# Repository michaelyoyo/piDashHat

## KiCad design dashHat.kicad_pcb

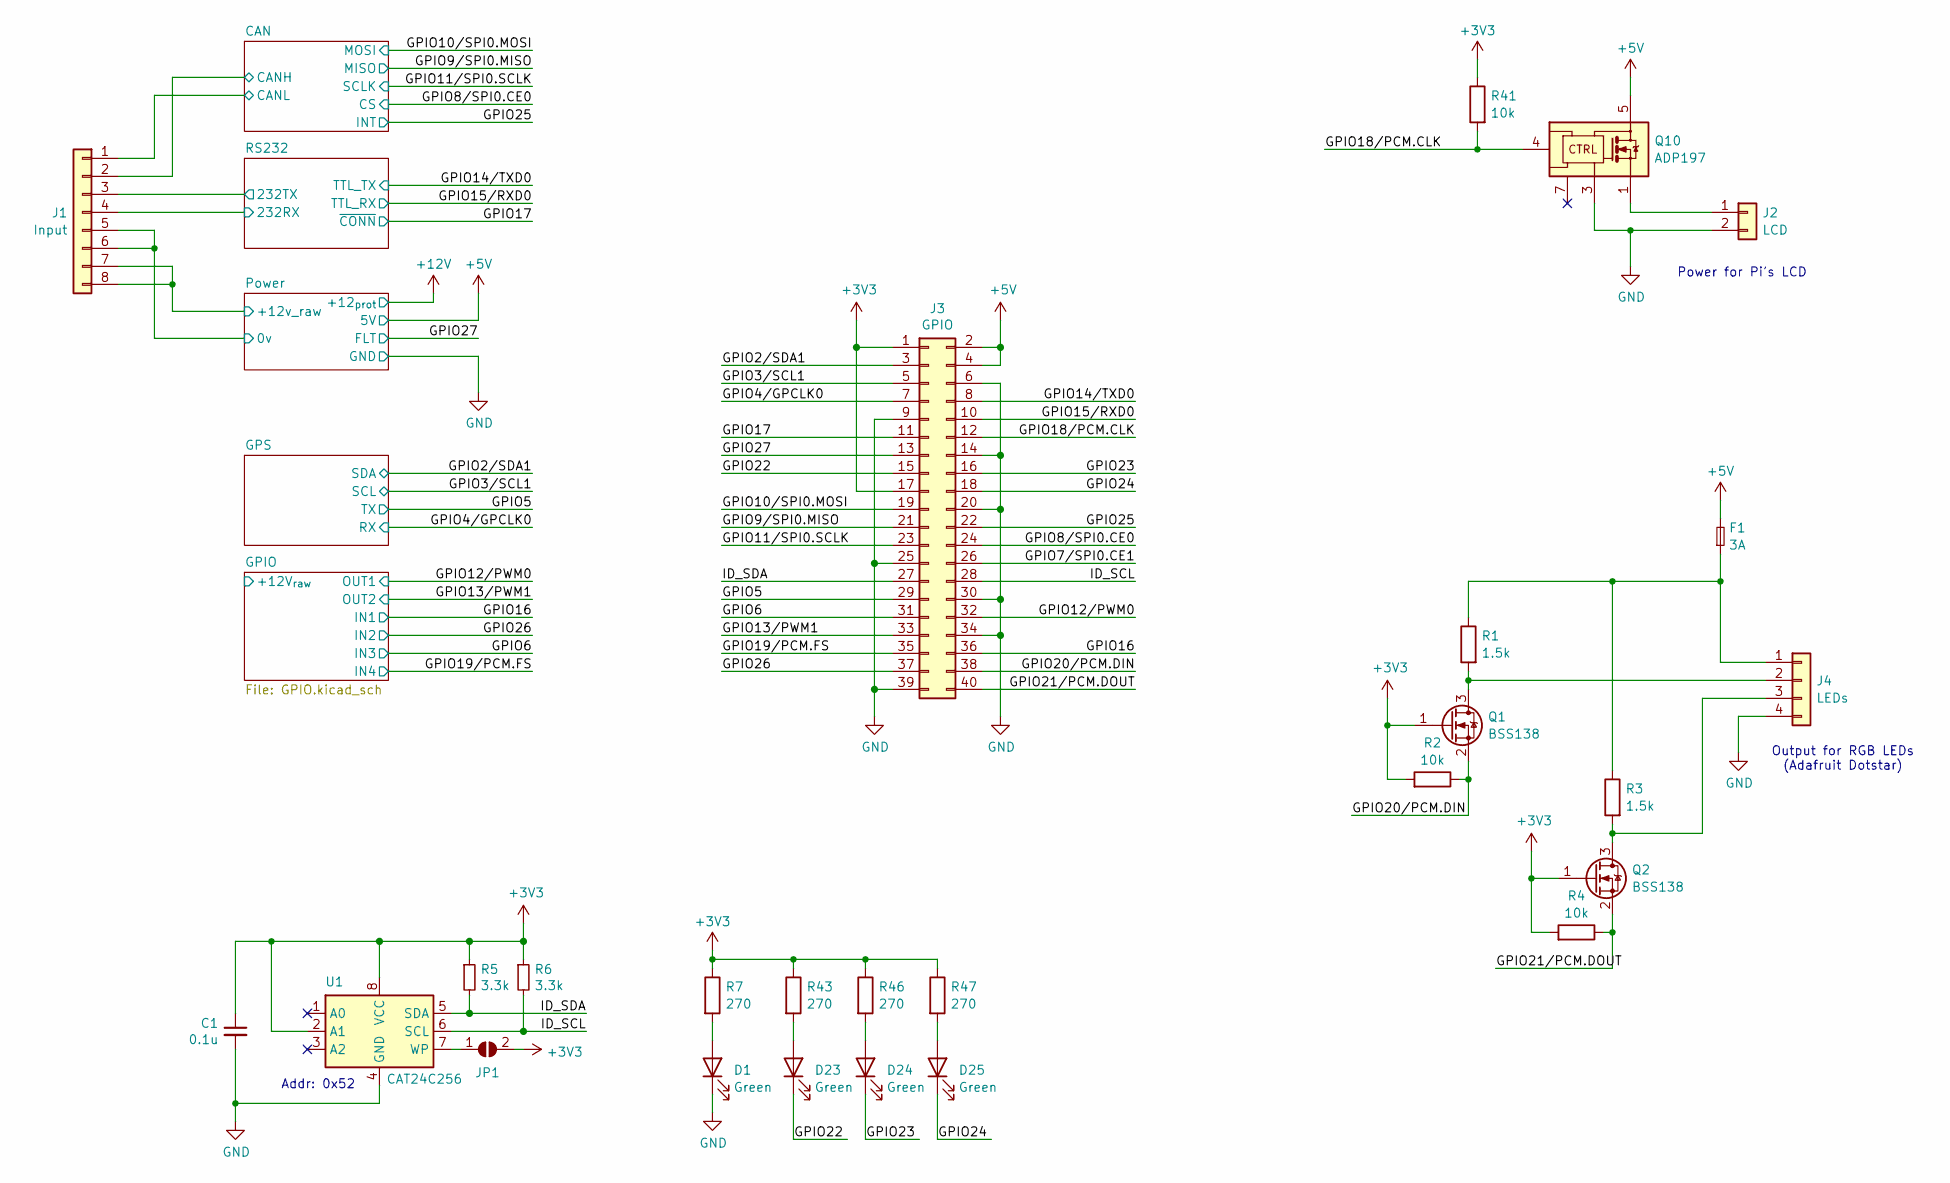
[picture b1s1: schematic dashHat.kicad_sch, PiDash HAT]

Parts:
C1: 0.1u; C_0603_1608Metric; Mfg Part Number CGA3E2X8R1E104K080AA
D1, D23, D24, D25: Green; LED_0603_1608Metric; Mfg Part Number HSMG-C190
F1: 3A; Fuse_1812_4532Metric; Mfg Part Number 0ZCG0260BF2B
J1: Input; Molex_Nano-Fit_105310-xx08_2x04_P2.50mm_Vertical; Mfg Part Number 105310-1108
J2: LCD; JST_XH_B2B-XH-A_1x02_P2.50mm_Vertical; Mfg Part Number --
J3: GPIO; PinSocket_2x20_P2.54mm_Vertical; Mfg Part Number SSQ-120-01-F-D
J4: LEDs; Molex_Nano-Fit_105310-xx04_2x02_P2.50mm_Vertical; Mfg Part Number 105310-1104
JP1: ID_WP; SolderJumper-2_P1.3mm_Open_RoundedPad1.0x1.5mm; Mfg Part Number --
Q1, Q2: BSS138; SOT-23; Mfg Part Number BSS138
Q10: ADP197; DFN-6-1EP_2x2mm_P0.65mm_EP1x1.6mm; Mfg Part Number ADP197ACPZN-01-R7
R1, R3: 1.5k; R_0603_1608Metric
R2, R4, R41: 10k; R_0603_1608Metric
R5, R6: 3.3k; R_0603_1608Metric
R7, R43, R46, R47: 270; R_0603_1608Metric
U1: CAT24C256; DFN-8-1EP_3x2mm_P0.5mm_EP1.36x1.46mm; Mfg Part Number CAT24C256HU4IGT3

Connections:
+3V3: C1.1, J3.1, J3.17, JP1.2 (B), Q1.1 (G), Q2.1 (G), R2.2, R4.2, R5.1, R6.1, R7.1, R41.1, R43.1, R46.1, R47.1, U1.2 (A1), U1.8 (VCC); also elsewhere on the board
+5V: F1.2, J3.2, J3.4, Q10.5 (VCC), Q10.6 (VCC); also elsewhere on the board
/CAN/CANH: J1.2; also elsewhere on the board
/CAN/CANL: J1.1; also elsewhere on the board
/GPIO2/SDA1: J3.3; also elsewhere on the board
/GPIO3/SCL1: J3.5; also elsewhere on the board
/GPIO4/GPCLK0: J3.7; also elsewhere on the board
/GPIO5: J3.29; also elsewhere on the board
/GPIO6: J3.31; also elsewhere on the board
/GPIO7/SPI0.CE1: J3.26
/GPIO8/SPI0.CE0: J3.24; also elsewhere on the board
/GPIO9/SPI0.MISO: J3.21; also elsewhere on the board
/GPIO10/SPI0.MOSI: J3.19; also elsewhere on the board
/GPIO11/SPI0.SCLK: J3.23; also elsewhere on the board
/GPIO12/PWM0: J3.32; also elsewhere on the board
/GPIO13/PWM1: J3.33; also elsewhere on the board
/GPIO14/TXD0: J3.8; also elsewhere on the board
/GPIO15/RXD0: J3.10; also elsewhere on the board
/GPIO16: J3.36; also elsewhere on the board
/GPIO17: J3.11; also elsewhere on the board
/GPIO18/PCM.CLK: J3.12, Q10.4 (EN), R41.2
/GPIO19/PCM.FS: J3.35; also elsewhere on the board
/GPIO20/PCM.DIN: J3.38, Q1.2 (S), R2.1
/GPIO21/PCM.DOUT: J3.40, Q2.2 (S), R4.1
/GPIO22: D23.1 (K), J3.15
/GPIO23: D24.1 (K), J3.16
/GPIO24: D25.1 (K), J3.18
/GPIO25: J3.22; also elsewhere on the board
/GPIO26: J3.37; also elsewhere on the board
/GPIO27: J3.13; also elsewhere on the board
/ID_SCL: J3.28, R6.2, U1.6 (SCL)
/ID_SDA: J3.27, R5.2, U1.5 (SDA)
/Power/+12v_raw: J1.7, J1.8; also elsewhere on the board
/RS232/232RX: J1.4; also elsewhere on the board
/RS232/232TX: J1.3; also elsewhere on the board
GND: C1.2, D1.1 (K), J1.5, J1.6, J2.2, J3.6, J3.9, J3.14, J3.20, J3.25, J3.30, J3.34, J3.39, J4.4, Q10.3 (GND), U1.4 (GND); also elsewhere on the board
unnamed: D1.2 (A), R7.2
unnamed: D23.2 (A), R43.2
unnamed: D24.2 (A), R46.2
unnamed: D25.2 (A), R47.2
unnamed: J2.1, Q10.1 (OUT), Q10.2 (OUT)
unnamed: F1.1, J4.1, R1.1, R3.1
unnamed: J4.2, Q1.3 (D), R1.2
unnamed: J4.3, Q2.3 (D), R3.2
unnamed: JP1.1 (A), U1.7 (WP)

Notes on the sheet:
Output for RGB LEDs (Adafruit Dotstar)
Addr: 0x52
Power for Pi's LCD

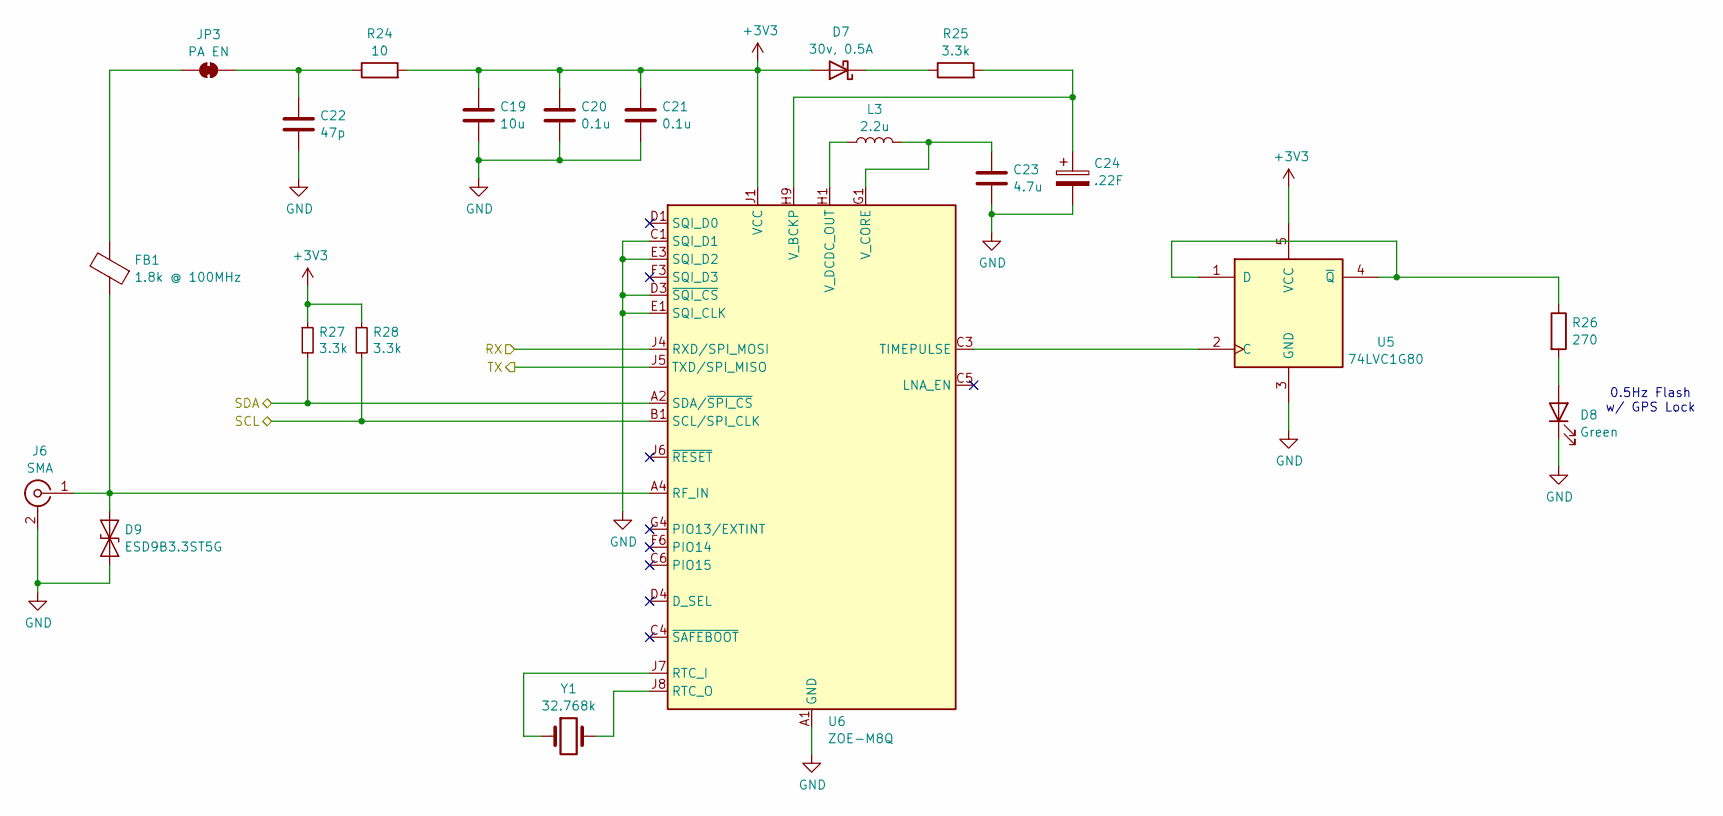
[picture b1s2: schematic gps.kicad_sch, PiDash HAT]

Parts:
C19: 10u; C_1206_3216Metric; Mfg Part Number CGA5L1X7R1C106K160AC
C20, C21: 0.1u; C_0603_1608Metric; Mfg Part Number CGA3E2X8R1E104K080AA
C22: 47p; C_0603_1608Metric; Mfg Part Number C0603C470K5RACAUTO
C23: 4.7u; C_0603_1608Metric; Mfg Part Number GCJ188C70J475KE02D
C24: .22F; DX_5R5HxxxxU_D11.5mm_P10.00mm; Mfg Part Number EDS224Z3R6H
D7: 30v, 0.5A; D_SOD-323HE; Mfg Part Number RSX051VYM30FHTR
D8: Green; LED_0603_1608Metric; Mfg Part Number HSMG-C190
D9: ESD9B3.3ST5G; D_SOD-923; Mfg Part Number ESD9R3.3ST5G
FB1: 1.8k @ 100MHz; L_0402_1005Metric; Mfg Part Number BLM15HD182SN1D
J6: SMA; SMA_Amphenol_132289_EdgeMount; Mfg Part Number 132289
JP3: PA EN; SolderJumper-2_P1.3mm_Open_RoundedPad1.0x1.5mm; Mfg Part Number --
L3: 2.2u; L_0806_2016Metric; Mfg Part Number LQM2MPN2R2NG0L
R24: 10; R_0603_1608Metric
R25, R27, R28: 3.3k; R_0603_1608Metric
R26: 270; R_0603_1608Metric
U5: 74LVC1G80; SOT-353_SC-70-5; Mfg Part Number 74LVC1G80GW,125
U6: ZOE-M8Q; ublox_ZOE_M8; Mfg Part Number ZOE-M8Q-0
Y1: 32.768k; Crystal_SMD_2012-2Pin_2.0x1.2mm; Mfg Part Number CM8V-T1A-32.768kHz-12.5pF-20PPM-TA-QC

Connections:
+3V3: C19.1, C20.1, C21.1, D7.2 (A), R24.2, R27.1, R28.1, U5.5 (VCC), U6.J1 (VCC), U6.J2 (VCC); also elsewhere on the board
/GPIO2/SDA1: R27.2, U6.A2 (SDA/~SPI_CS); also elsewhere on the board
/GPIO3/SCL1: R28.2, U6.B1 (SCL/SPI_CLK); also elsewhere on the board
/GPIO4/GPCLK0: U6.J4 (RXD/SPI_MOSI); also elsewhere on the board
/GPIO5: U6.J5 (TXD/SPI_MISO); also elsewhere on the board
GND: C19.2, C20.2, C21.2, C22.2, C23.2, C24.2, D8.1 (K), D9.1 (A1), J6.2 (Ext), U5.3 (GND), U6.A1 (GND), U6.A3 (GND), U6.A5 (GND), U6.A7 (GND), U6.A8 (GND), U6.A9 (GND), U6.B9 (GND), U6.C1 (SQI_D1), U6.C7 (GND), U6.C9 (GND), U6.D3 (~SQI_CS), U6.D6 (GND), U6.D9 (GND), U6.E1 (SQI_CLK), U6.E3 (SQI_D2), U6.E7 (GND), U6.F7 (GND), U6.G3 (GND), U6.G6 (GND), U6.G7 (GND), U6.J3 (GND), U6.J9 (GND); also elsewhere on the board
unnamed: D7.1 (K), R25.1
unnamed: D8.2 (A), R26.2
unnamed: D9.2 (A2), FB1.1, J6.1 (In), U6.A4 (RF_IN)
unnamed: C22.1, JP3.1 (A), R24.1
unnamed: FB1.2, JP3.2 (B)
unnamed: U5.2 (C), U6.C3 (TIMEPULSE)
unnamed: R26.1, U5.1 (D), U5.4 (~Q)
unnamed: U6.J7 (RTC_I), Y1.1
unnamed: U6.J8 (RTC_O), Y1.2
unnamed: C24.1, R25.2, U6.H9 (V_BCKP)
unnamed: C23.1, L3.2, U6.G1 (V_CORE)
unnamed: L3.1, U6.H1 (V_DCDC_OUT)

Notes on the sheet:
0.5Hz Flash w/ GPS Lock

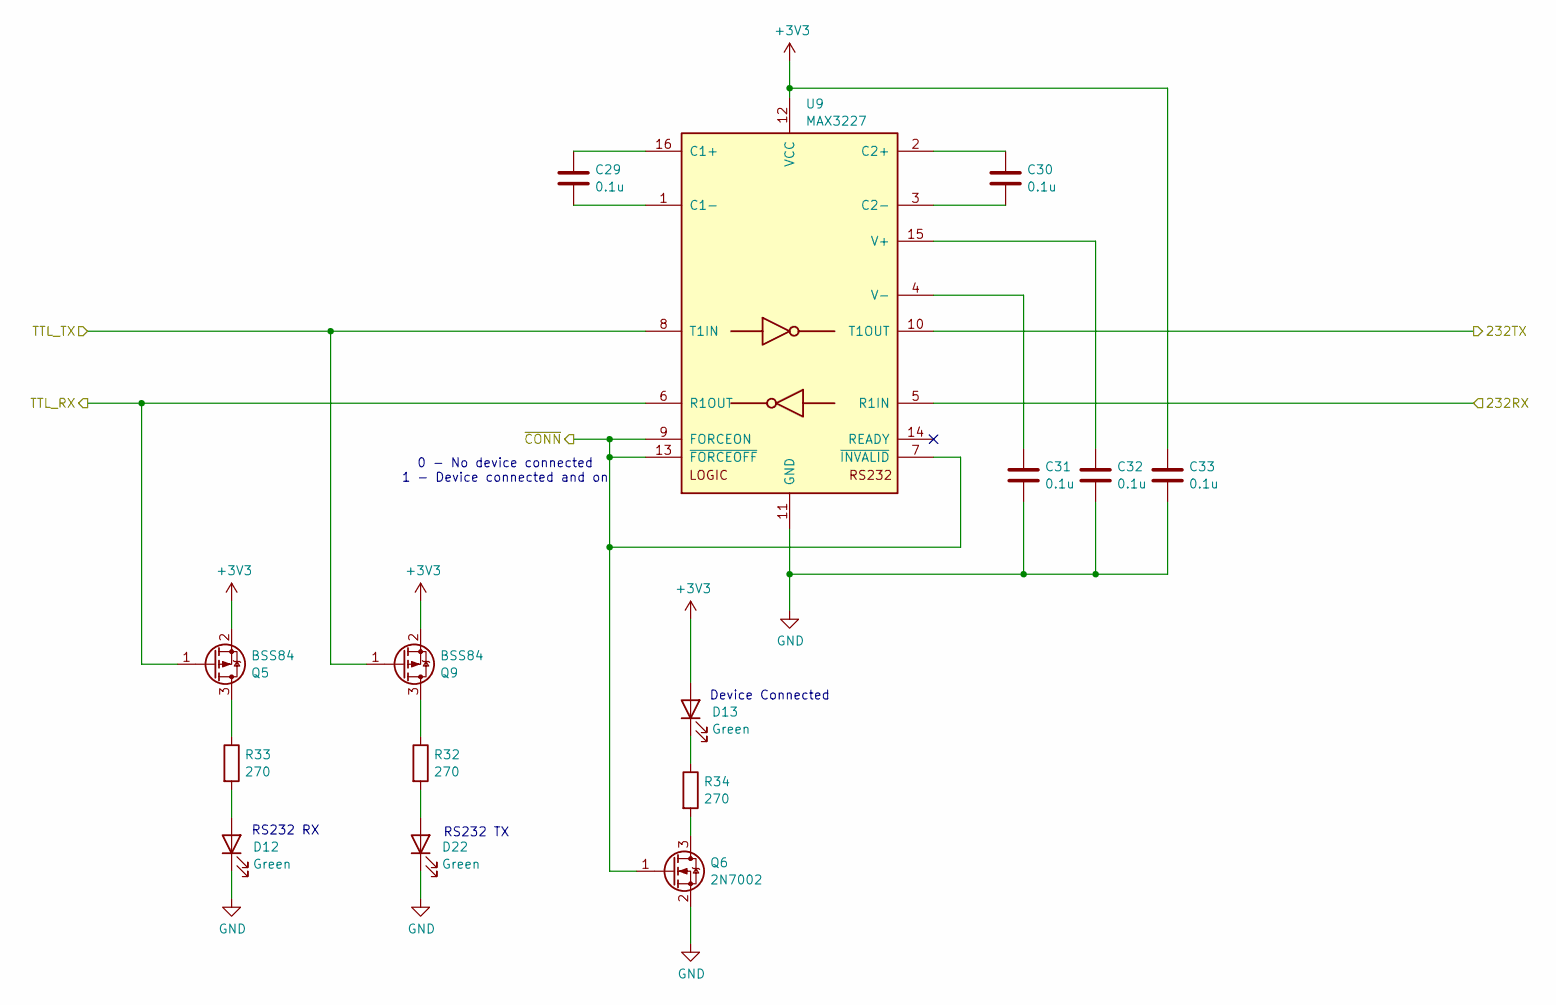
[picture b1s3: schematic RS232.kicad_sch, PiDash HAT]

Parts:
C29, C30, C31, C32, C33: 0.1u; C_0603_1608Metric; Mfg Part Number CGA3E2X8R1E104K080AA
D12, D13, D22: Green; LED_0603_1608Metric; Mfg Part Number HSMG-C190
Q5, Q9: BSS84; SOT-23; Mfg Part Number BSS84
Q6: 2N7002; SOT-23; Mfg Part Number 2N7002
R32, R33, R34: 270; R_0603_1608Metric
U9: MAX3227; QFN-16-1EP_5x5mm_P0.8mm_EP2.7x2.7mm; Mfg Part Number MAX3226EETE+

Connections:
+3V3: C33.1, D13.2 (A), Q5.2 (S), Q9.2 (S), U9.12 (VCC); also elsewhere on the board
/GPIO14/TXD0: Q9.1 (G), U9.8 (T1IN); also elsewhere on the board
/GPIO15/RXD0: Q5.1 (G), U9.6 (R1OUT); also elsewhere on the board
/GPIO17: Q6.1 (G), U9.7 (~INVALID), U9.9 (FORCEON), U9.13 (~FORCEOFF); also elsewhere on the board
/RS232/232RX: U9.5 (R1IN); also elsewhere on the board
/RS232/232TX: U9.10 (T1OUT); also elsewhere on the board
GND: C31.2, C32.2, C33.2, D12.1 (K), D22.1 (K), Q6.2 (S), U9.11 (GND); also elsewhere on the board
unnamed: D12.2 (A), R33.2
unnamed: D13.1 (K), R34.1
unnamed: D22.2 (A), R32.2
unnamed: Q5.3 (D), R33.1
unnamed: Q6.3 (D), R34.2
unnamed: Q9.3 (D), R32.1
unnamed: C29.1, U9.16 (C1+)
unnamed: C29.2, U9.1 (C1-)
unnamed: C30.1, U9.2 (C2+)
unnamed: C30.2, U9.3 (C2-)
unnamed: C32.1, U9.15 (V+)
unnamed: C31.1, U9.4 (V-)

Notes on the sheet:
RS232 TX
0 - No device connected 1 - Device connected and on
RS232 RX
Device Connected

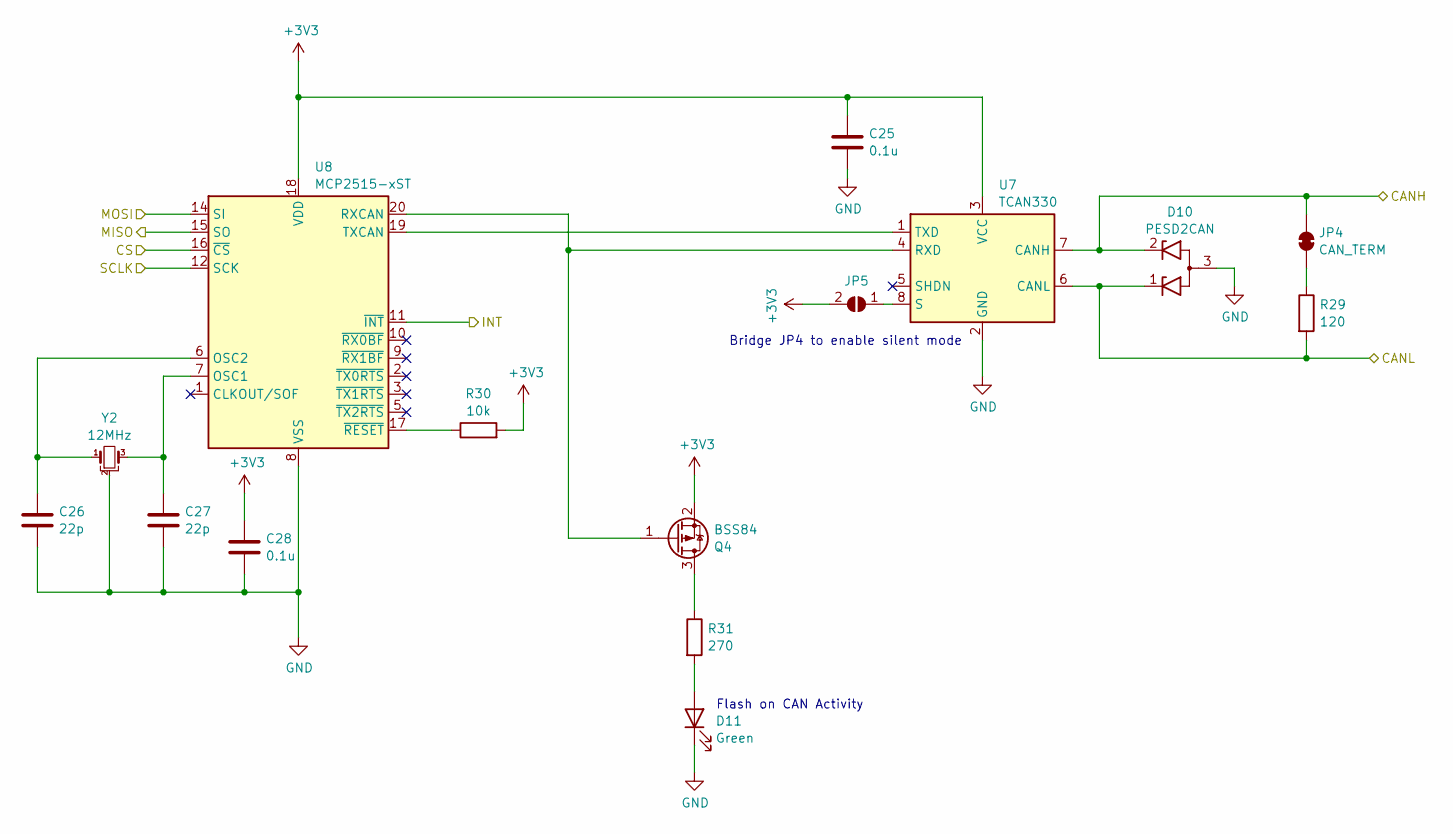
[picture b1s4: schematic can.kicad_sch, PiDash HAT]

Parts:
C25, C28: 0.1u; C_0603_1608Metric; Mfg Part Number CGA3E2X8R1E104K080AA
C26, C27: 22p; C_0603_1608Metric; Mfg Part Number VJ0603A220KXAAC
D10: PESD2CAN; SOT-23; Mfg Part Number PESD2CANFD36VT-QR
D11: Green; LED_0603_1608Metric; Mfg Part Number HSMG-C190
JP4: CAN_TERM; SolderJumper-2_P1.3mm_Bridged_RoundedPad1.0x1.5mm; Mfg Part Number --
JP5: CAN_SILENT; SolderJumper-2_P1.3mm_Open_RoundedPad1.0x1.5mm; Mfg Part Number --
Q4: BSS84; SOT-23; Mfg Part Number BSS84
R29: 120; R_0603_1608Metric
R30: 10k; R_0603_1608Metric
R31: 270; R_0603_1608Metric
U7: TCAN330; SOT-23-8; Mfg Part Number TCAN330DCNR
U8: MCP2515-xST; QFN-20-1EP_4x4mm_P0.5mm_EP2.7x2.7mm; Mfg Part Number MCP2515-I/ML
Y2: 12MHz; Crystal_SMD_3225-4Pin_3.2x2.5mm; Mfg Part Number FL1200112

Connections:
+3V3: C25.1, C28.1, JP5.2 (B), Q4.2 (S), R30.2, U7.3 (VCC), U8.18 (VDD); also elsewhere on the board
/CAN/CANH: D10.2 (K2), JP4.2 (B), U7.7 (CANH); also elsewhere on the board
/CAN/CANL: D10.1 (K1), R29.2, U7.6 (CANL); also elsewhere on the board
/GPIO8/SPI0.CE0: U8.16 (~CS); also elsewhere on the board
/GPIO9/SPI0.MISO: U8.15 (SO); also elsewhere on the board
/GPIO10/SPI0.MOSI: U8.14 (SI); also elsewhere on the board
/GPIO11/SPI0.SCLK: U8.12 (SCK); also elsewhere on the board
/GPIO25: U8.11 (~INT); also elsewhere on the board
GND: C25.2, C26.2, C27.2, C28.2, D10.3 (A), D11.1 (K), U7.2 (GND), U8.8 (VSS), U8.21 (EP), Y2.2; also elsewhere on the board
unnamed: D11.2 (A), R31.2
unnamed: JP4.1 (A), R29.1
unnamed: JP5.1 (A), U7.8 (S)
unnamed: Q4.3 (D), R31.1
unnamed: Q4.1 (G), U7.4 (RXD), U8.20 (RXCAN)
unnamed: U7.1 (TXD), U8.19 (TXCAN)
unnamed: C27.1, U8.7 (OSC1), Y2.3
unnamed: C26.1, U8.6 (OSC2), Y2.1
unnamed: R30.1, U8.17 (~RESET)

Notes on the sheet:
Flash on CAN Activity
Bridge JP4 to enable silent mode

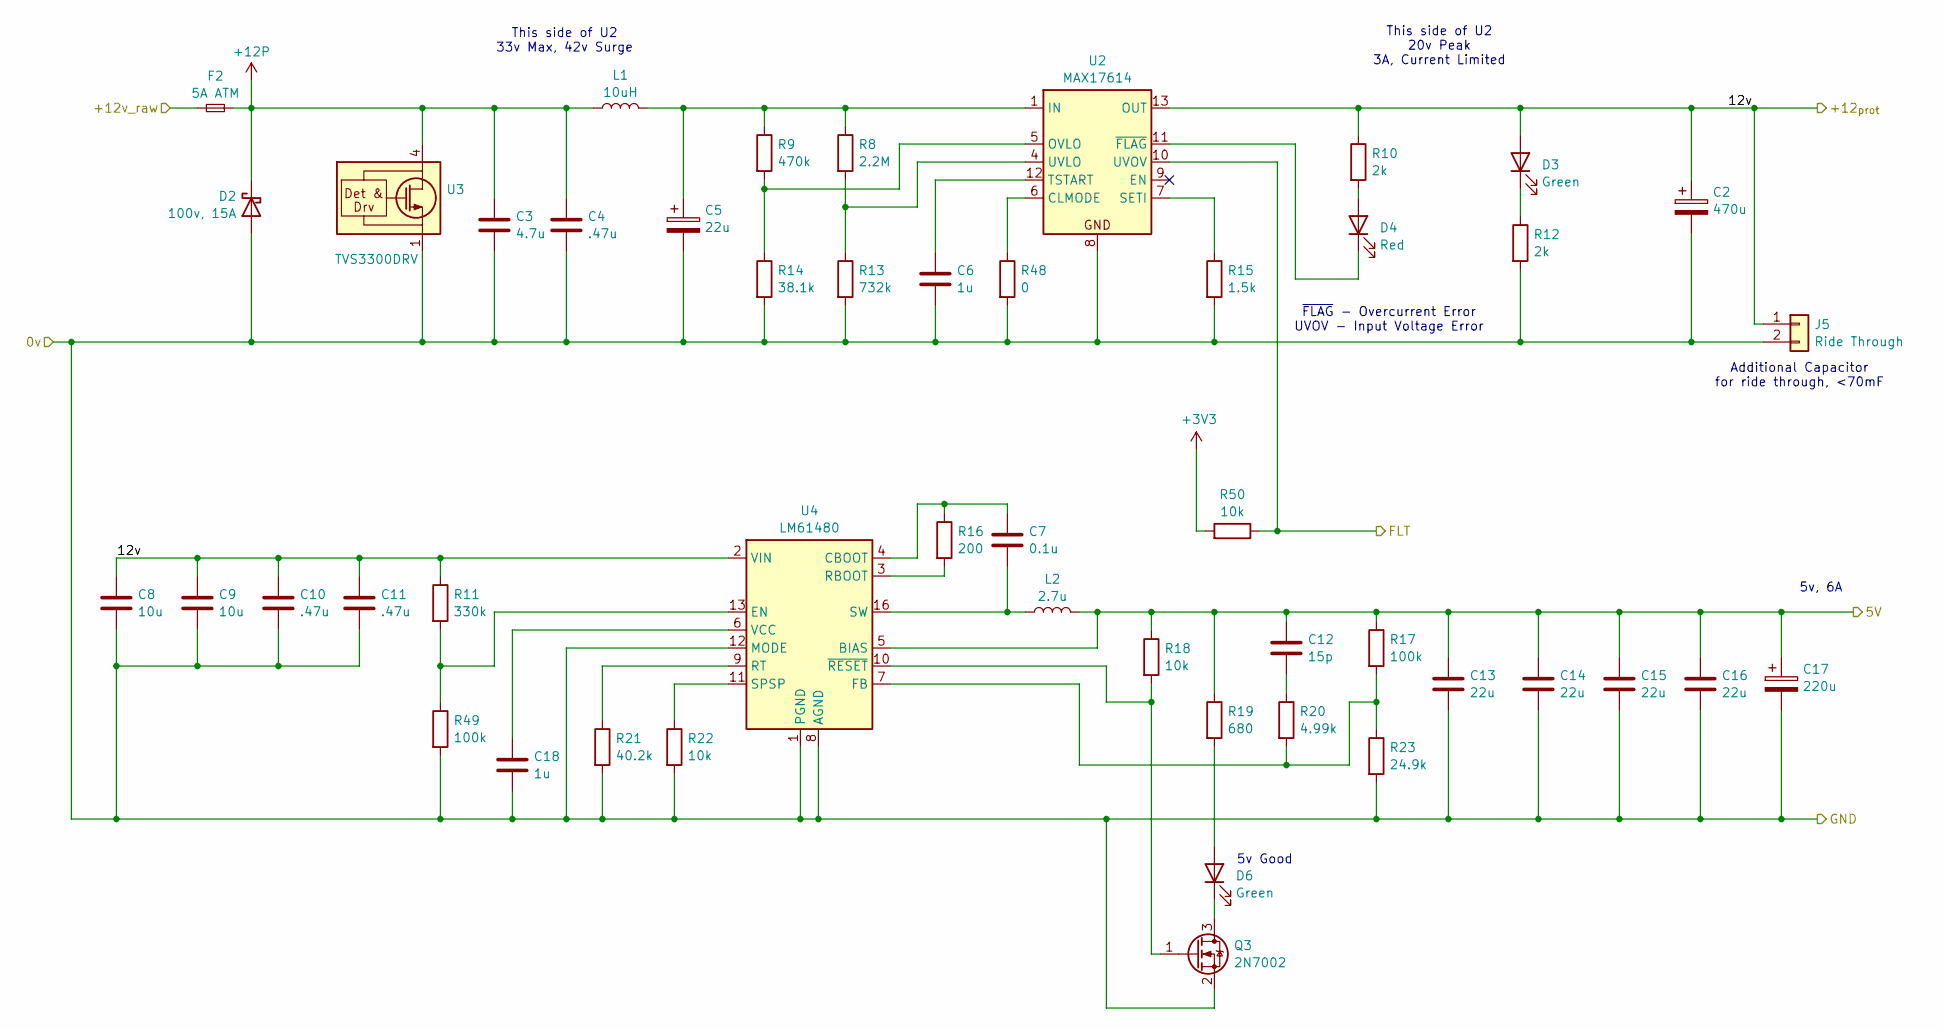
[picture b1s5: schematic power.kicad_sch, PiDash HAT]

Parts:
C2: 470u; CP_Radial_D8.0mm_P3.50mm; Mfg Part Number EEU-FR1C471
C3: 4.7u; C_1206_3216Metric; Mfg Part Number CGA5L3X7R1H475K160AE
C4, C10, C11: .47u; C_0805_2012Metric; Mfg Part Number GCM21BR71H474KA55K
C5: 22u; CP_Radial_D5.0mm_P2.00mm; Mfg Part Number EEA-GA1C220H
C6: 1u; C_0603_1608Metric; Mfg Part Number 06035C104K4Z2A
C7: 0.1u; C_0603_1608Metric; Mfg Part Number CGA3E2X8R1E104K080AA
C8, C9: 10u; C_1210_3225Metric; Mfg Part Number UMK325AB7106KM-T
C12: 15p; C_0603_1608Metric; Mfg Part Number C0603C150K5RACAUTO
C13, C14, C15, C16: 22u; C_1210_3225Metric; Mfg Part Number CGA6P3X7R1E226M250AE
C17: 220u; CP_Radial_D6.3mm_P2.50mm; Mfg Part Number 860240273005
C18: 1u; C_0603_1608Metric; Mfg Part Number MSAST168SB7105KTNA01
D2: 100v, 15A; TO-277A; Mfg Part Number YQ15RSM10SDTL1
D3, D6: Green; LED_0603_1608Metric; Mfg Part Number HSMG-C190
D4: Red; LED_0603_1608Metric; Mfg Part Number HSMS-C190
F2: 5A ATM; Fuseholder_Blade_Mini_Keystone_3568; Mfg Part Number 3568
J5: Ride Through; JST_PH_B2B-PH-K_1x02_P2.00mm_Vertical; Mfg Part Number --
L1: 10uH; L_Coilcraft_XxL4030; Mfg Part Number XGL4030-103MEC
L2: 2.7u; L_Coilcraft_XAL7030-272; Mfg Part Number XAL7030-272MEC
Q3: 2N7002; SOT-23; Mfg Part Number 2N7002
R8: 2.2M; R_0603_1608Metric
R9: 470k; R_0603_1608Metric
R10, R12: 2k; R_0603_1608Metric
R11: 330k; R_0603_1608Metric
R13: 732k; R_0603_1608Metric
R14: 38.1k; R_0603_1608Metric
R15: 1.5k; R_0603_1608Metric
R16: 200; R_0603_1608Metric
R17, R49: 100k; R_0603_1608Metric
R18, R22, R50: 10k; R_0603_1608Metric
R19: 680; R_0603_1608Metric
R20: 4.99k; R_0603_1608Metric
R21: 40.2k; R_0603_1608Metric
R23: 24.9k; R_0603_1608Metric
R48: 0; R_0603_1608Metric
U2: MAX17614; TQFN-20-1EP_4x4mm_P0.5mm_EP2.9x2.9mm_ThermalVias; Mfg Part Number MAX17614ATP+
U3: TVS3300DRV; WSON-6-1EP_2x2mm_P0.65mm_EP1x1.6mm; Mfg Part Number TVS3300DRVR
U4: LM61480; LM6x4xx Buck Converter; Mfg Part Number LM61480RPHR

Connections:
+3V3: R50.2; also elsewhere on the board
+5V: C12.2, C13.1, C14.1, C15.1, C16.1, C17.1, L2.2, R17.1, R18.1, R19.1, U4.5 (BIAS); also elsewhere on the board
+12P: C3.1, C4.1, D2.1 (K), F2.2, L1.1, U3.4 (IN), U3.5 (IN), U3.6 (IN); also elsewhere on the board
+12V: C2.1, C8.1, C9.1, C10.1, C11.1, D3.2 (A), J5.1, R10.1, R11.1, U2.13 (OUT), U2.14 (OUT), U2.15 (OUT), U4.2 (VIN), U4.14 (VIN); also elsewhere on the board
/GPIO27: R50.1, U2.10 (UVOV); also elsewhere on the board
/Power/+12v_raw: F2.1; also elsewhere on the board
GND: C2.2, C3.2, C4.2, C5.2, C6.2, C8.2, C9.2, C10.2, C11.2, C13.2, C14.2, C15.2, C16.2, C17.2, C18.2, D2.2 (A), J5.2, Q3.2 (S), R12.2, R13.2, R14.2, R15.2, R21.2, R22.2, R23.2, R48.2, R49.2, U2.8, U2.21 (EP), U3.1 (GND), U3.2 (GND), U3.3 (GND), U3.7 (GND), U4.1 (PGND), U4.8 (AGND), U4.12 (MODE), U4.15 (PGND); also elsewhere on the board
IN: C5.1, L1.2, R8.1, R9.1, U2.1 (IN), U2.2 (IN), U2.3 (IN)
unnamed: C12.1, R20.1
unnamed: D3.1 (K), R12.1
unnamed: D4.2 (A), R10.2
unnamed: D4.1 (K), U2.11 (~FLAG)
unnamed: D6.2 (A), R19.2
unnamed: D6.1 (K), Q3.3 (D)
unnamed: Q3.1 (G), R18.2, U4.10 (~RESET)
unnamed: R48.1, U2.6 (CLMODE)
unnamed: R9.2, R14.1, U2.5 (OVLO)
unnamed: R15.1, U2.7 (SETI)
unnamed: C6.1, U2.12 (TSTART)
unnamed: R8.2, R13.1, U2.4 (UVLO)
unnamed: C7.1, R16.1, U4.4 (CBOOT)
unnamed: R11.2, R49.1, U4.13 (EN)
unnamed: R17.2, R20.2, R23.1, U4.7 (FB)
unnamed: R16.2, U4.3 (RBOOT)
unnamed: R21.1, U4.9 (RT)
unnamed: R22.1, U4.11 (SPSP)
unnamed: C7.2, L2.1, U4.16 (SW)
unnamed: C18.1, U4.6 (VCC)

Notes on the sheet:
This side of U2 33v Max, 42v Surge
5v, 6A
Additional Capacitor for ride through, <70mF
This side of U2 20v Peak 3A, Current Limited
~{FLAG} - Overcurrent Error UVOV - Input Voltage Error
5v Good

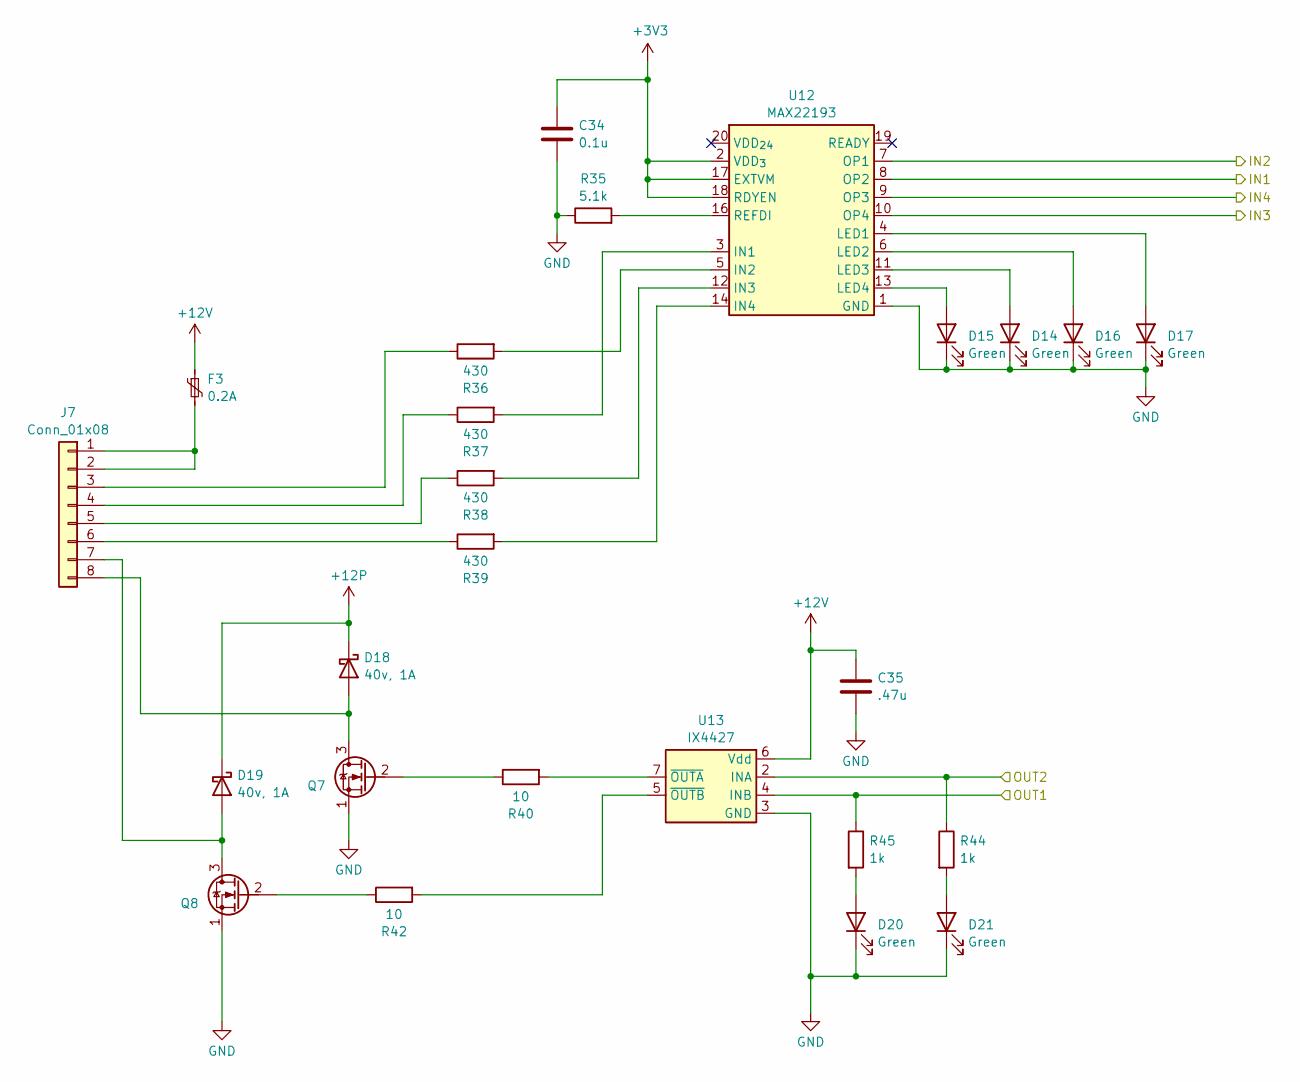
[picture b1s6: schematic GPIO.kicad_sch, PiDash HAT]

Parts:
C34: 0.1u; C_0603_1608Metric; Mfg Part Number CGA3E2X8R1E104K080AA
C35: .47u; C_0805_2012Metric; Mfg Part Number GCM21BR71H474KA55K
D14, D15, D16, D17, D20, D21: Green; LED_0603_1608Metric; Mfg Part Number HSMG-C190
D18, D19: 40v, 1A; D_SOD-323F; Mfg Part Number PMEG4010EJ,115
F3: 0.2A; Fuse_1812_4532Metric; Mfg Part Number MINISMDC020F-2
J7: Conn_01x08; Molex_Nano-Fit_105309-xx08_1x08_P2.50mm_Vertical; Mfg Part Number 105309-1208
Q7, Q8: Infineon_PG-TDSON-8_6.15x5.15mm; Mfg Part Number SIRA54ADP-T1-RE3
R35: 5.1k; R_0603_1608Metric
R36, R37, R38, R39: 430; R_0603_1608Metric
R40, R42: 10; R_0603_1608Metric
R44, R45: 1k; R_0603_1608Metric
U12: MAX22193; TQFN-20-1EP_4x4mm_P0.5mm_EP2.1x2.1mm; Mfg Part Number MAX22193ATP+
U13: IX4427; DFN-8-1EP_3x3mm_P0.65mm_EP1.7x2.05mm; Mfg Part Number IX4427MTR

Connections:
+3V3: C34.1, U12.2 (VDD_{3}), U12.17 (EXTVM), U12.18 (RDYEN); also elsewhere on the board
+12P: D18.1 (K), D19.1 (K); also elsewhere on the board
+12V: C35.1, F3.1, U13.6 (Vdd); also elsewhere on the board
/GPIO6: U12.10 (OP4); also elsewhere on the board
/GPIO12/PWM0: R45.1, U13.4 (INB); also elsewhere on the board
/GPIO13/PWM1: R44.1, U13.2 (INA); also elsewhere on the board
/GPIO16: U12.8 (OP2); also elsewhere on the board
/GPIO19/PCM.FS: U12.9 (OP3); also elsewhere on the board
/GPIO26: U12.7 (OP1); also elsewhere on the board
GND: C34.2, C35.2, D14.1 (K), D15.1 (K), D16.1 (K), D17.1 (K), D20.1 (K), D21.1 (K), Q7.1 (S), Q8.1 (S), R35.1, U12.1 (GND), U12.15 (GND), U12.21 (GND), U13.3 (GND); also elsewhere on the board
unnamed: D14.2 (A), U12.11 (LED3)
unnamed: D15.2 (A), U12.13 (LED4)
unnamed: D16.2 (A), U12.6 (LED2)
unnamed: D17.2 (A), U12.4 (LED1)
unnamed: D18.2 (A), J7.8, Q7.3 (D)
unnamed: D19.2 (A), J7.7, Q8.3 (D)
unnamed: D20.2 (A), R45.2
unnamed: D21.2 (A), R44.2
unnamed: F3.2, J7.1, J7.2
unnamed: J7.3, R36.1
unnamed: J7.4, R37.1
unnamed: J7.5, R38.1
unnamed: J7.6, R39.1
unnamed: Q7.2 (G), R40.1
unnamed: Q8.2 (G), R42.1
unnamed: R37.2, U12.3 (IN1)
unnamed: R36.2, U12.5 (IN2)
unnamed: R38.2, U12.12 (IN3)
unnamed: R39.2, U12.14 (IN4)
unnamed: R35.2, U12.16 (REFDI)
unnamed: R40.2, U13.7 (~OUTA)
unnamed: R42.2, U13.5 (~OUTB)

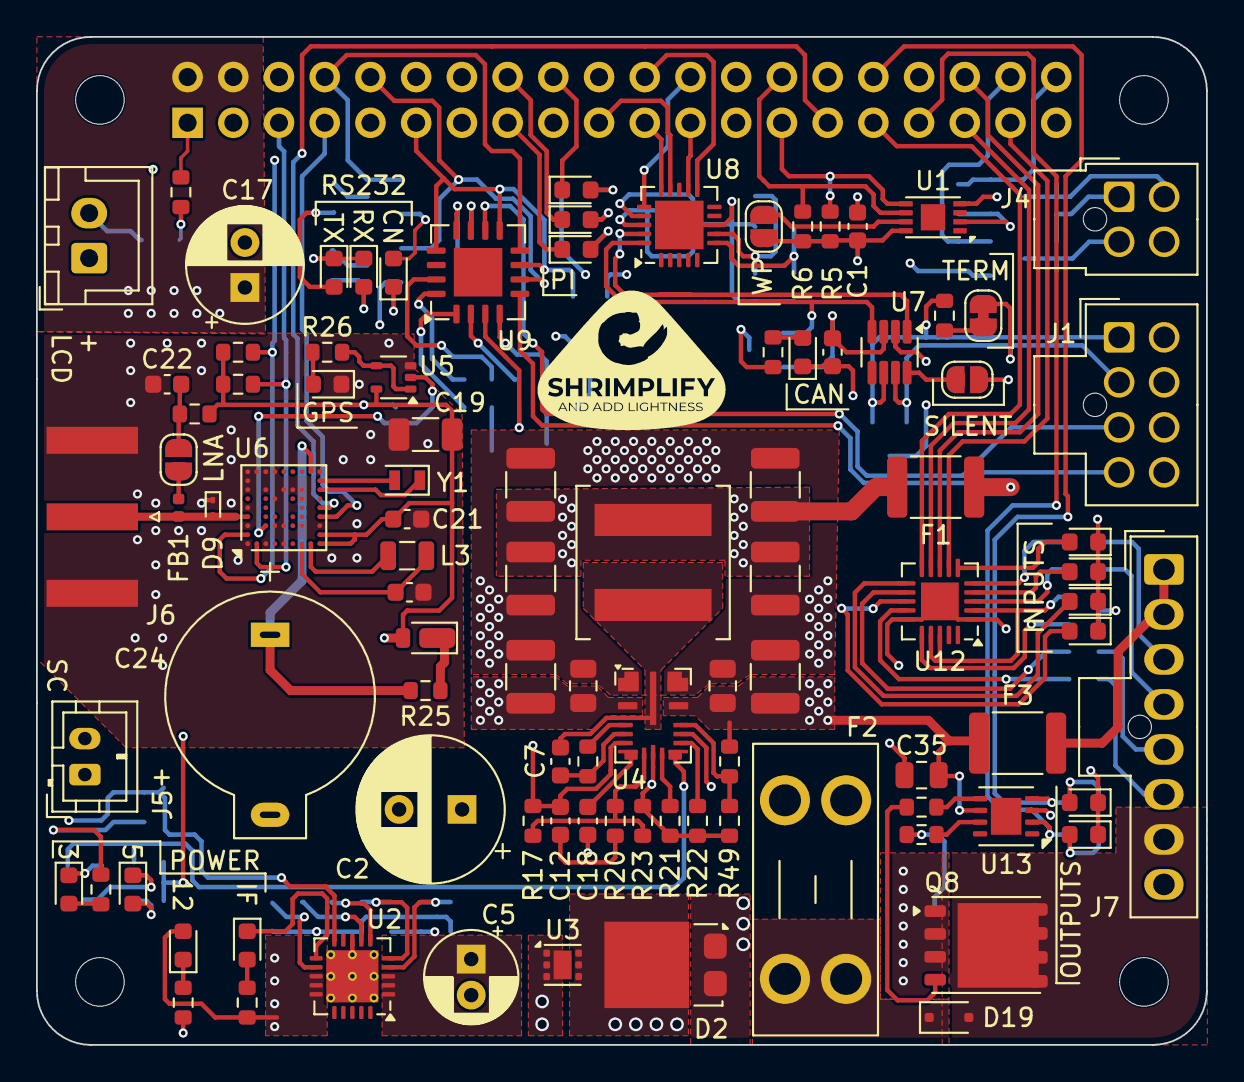
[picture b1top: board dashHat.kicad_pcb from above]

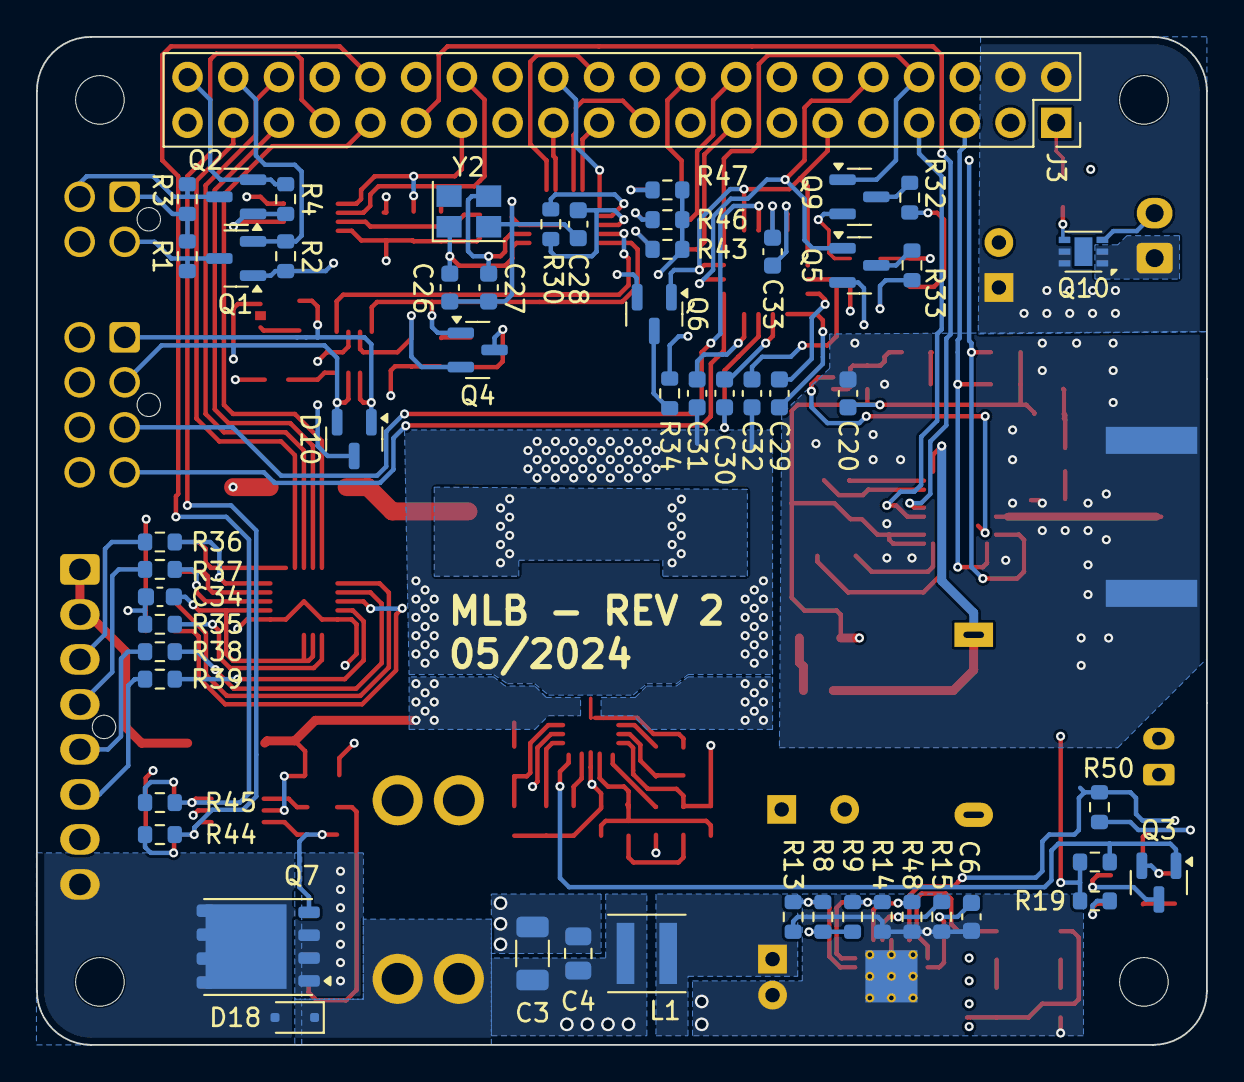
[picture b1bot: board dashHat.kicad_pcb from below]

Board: 4 copper layers, 65.0 x 56.0 mm, 154 parts (54 on the bottom side), 122 nets.

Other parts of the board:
MH1, MH2, MH3, MH4: MountingHole_2.7mm_M2.5

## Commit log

2024-05-07 added 4 inputs and 2 pwm outputs, completed routing
2024-05-07 revised schematic after initial layout - all connectors are vertical - increased current handling of outputs - replaced mechanical relay with ssr - jumper to disable gps antenna power
2024-05-11 second pass at layout complete
2024-05-11 add a version, add uart test pads to gps, sent for manufacturing
2024-05-12 filled in mfg part number for ordering
2024-05-12 added missing 3d models, fussed with the silkscreen more
2024-05-28 bug fixes from testing
2024-05-31 fixes from testing, updated for pi5
2024-05-31 added a switch to the lcd, and feedback from the 12v input to the pi
2024-05-31 selectable current limit mode
2024-05-31 fix up silkscreen
2024-05-31 switch can crystal to 12MHz
2024-05-31 last tweaks
2024-06-11 update resistors to more commmon values
2024-06-22 flip logic on rs232 conn led
2024-06-26 remove vf led, add en divider to 5v regulator to fix sequencing
